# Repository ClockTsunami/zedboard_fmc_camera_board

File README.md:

zedboard_fmc_camera_board
=========================

fmc lpc camera board for zedboard

eagle library initially get from:

code.danstrother.com/eagle-lbr/dan-xilinx.lbr

https://github.com/zynqgeek/Zedboard-Eagle-Library.git

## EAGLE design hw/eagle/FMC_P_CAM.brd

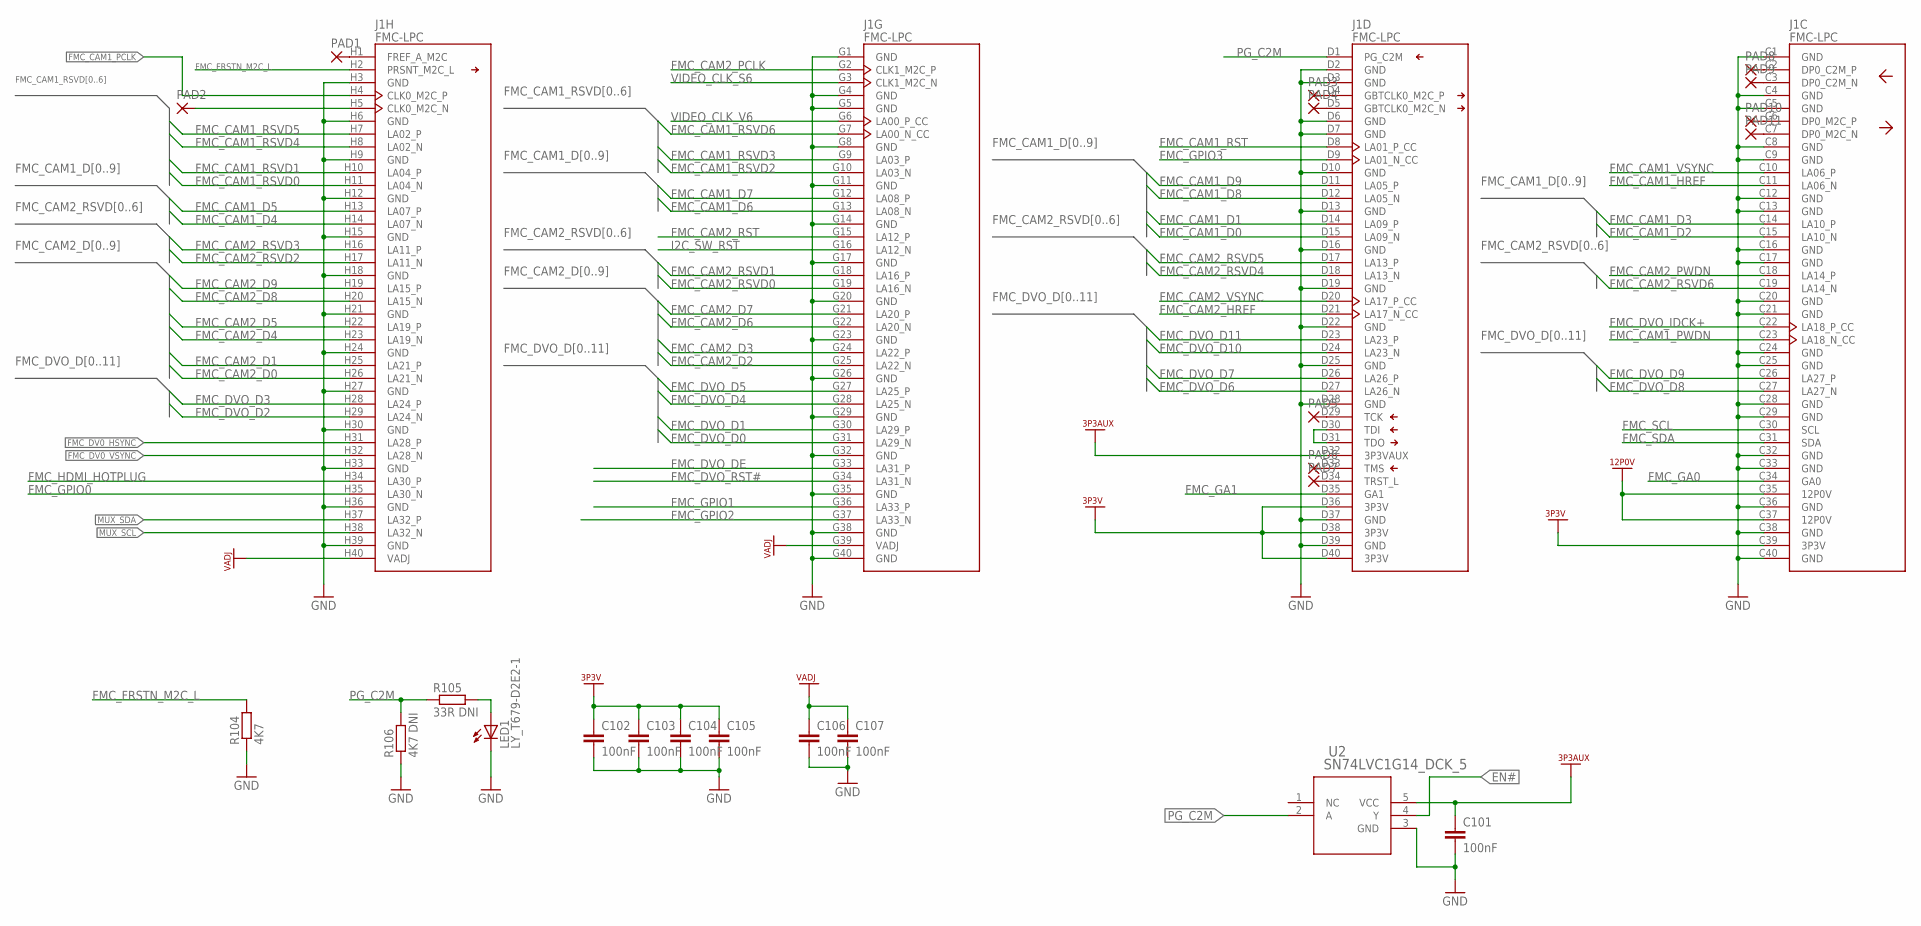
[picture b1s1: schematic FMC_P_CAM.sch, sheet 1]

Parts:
C101, C102, C103, C104, C105, C106, C107: 100nF; C0603
J1: FMC-LPC; FMC-LPC-MALE
LED1: LY_T679-D2E2-1; PLCC2
PAD1, PAD2, PAD3, PAD4, PAD5, PAD6, PAD7, PAD8, PAD9, PAD10, PAD11: 1,6/0,8
R104: 4K7; R0603
R105: 33R DNI; R0603
R106: 4K7 DNI; R0603
U2: SN74LVC1G14_DCK_5; DCK5

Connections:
3P3AUX: C101.1, J1.D32 (3P3VAUX), U2.5 (VCC)
3P3V: C102.1, C103.1, C104.1, C105.1, J1.C39 (3P3V), J1.D36 (3P3V), J1.D38 (3P3V), J1.D40 (3P3V); also elsewhere on the board
12P0V: J1.C35 (12P0V), J1.C37 (12P0V); also elsewhere on the board
EN#: U2.4 (Y); also elsewhere on the board
FMC_CAM1_D0: J1.D15 (LA09_N); also elsewhere on the board
FMC_CAM1_D1: J1.D14 (LA09_P); also elsewhere on the board
FMC_CAM1_D2: J1.C15 (LA10_N); also elsewhere on the board
FMC_CAM1_D3: J1.C14 (LA10_P); also elsewhere on the board
FMC_CAM1_D4: J1.H14 (LA07_N); also elsewhere on the board
FMC_CAM1_D5: J1.H13 (LA07_P); also elsewhere on the board
FMC_CAM1_D6: J1.G13 (LA08_N); also elsewhere on the board
FMC_CAM1_D7: J1.G12 (LA08_P); also elsewhere on the board
FMC_CAM1_D8: J1.D12 (LA05_N); also elsewhere on the board
FMC_CAM1_D9: J1.D11 (LA05_P); also elsewhere on the board
FMC_CAM1_HREF: J1.C11 (LA06_N); also elsewhere on the board
FMC_CAM1_PCLK: J1.H4 (CLK0_M2C_P); also elsewhere on the board
FMC_CAM1_PWDN: J1.C23 (LA18_N_CC); also elsewhere on the board
FMC_CAM1_RST: J1.D8 (LA01_P_CC); also elsewhere on the board
FMC_CAM1_RSVD0: J1.H11 (LA04_N); also elsewhere on the board
FMC_CAM1_RSVD1: J1.H10 (LA04_P); also elsewhere on the board
FMC_CAM1_RSVD2: J1.G10 (LA03_N); also elsewhere on the board
FMC_CAM1_RSVD3: J1.G9 (LA03_P); also elsewhere on the board
FMC_CAM1_RSVD4: J1.H8 (LA02_N); also elsewhere on the board
FMC_CAM1_RSVD5: J1.H7 (LA02_P); also elsewhere on the board
FMC_CAM1_RSVD6: J1.G7 (LA00_N_CC); also elsewhere on the board
FMC_CAM1_VSYNC: J1.C10 (LA06_P); also elsewhere on the board
FMC_CAM2_D0: J1.H26 (LA21_N); also elsewhere on the board
FMC_CAM2_D1: J1.H25 (LA21_P); also elsewhere on the board
FMC_CAM2_D2: J1.G25 (LA22_N); also elsewhere on the board
FMC_CAM2_D3: J1.G24 (LA22_P); also elsewhere on the board
FMC_CAM2_D4: J1.H23 (LA19_N); also elsewhere on the board
FMC_CAM2_D5: J1.H22 (LA19_P); also elsewhere on the board
FMC_CAM2_D6: J1.G22 (LA20_N); also elsewhere on the board
FMC_CAM2_D7: J1.G21 (LA20_P); also elsewhere on the board
FMC_CAM2_D8: J1.H20 (LA15_N); also elsewhere on the board
FMC_CAM2_D9: J1.H19 (LA15_P); also elsewhere on the board
FMC_CAM2_HREF: J1.D21 (LA17_N_CC); also elsewhere on the board
FMC_CAM2_PCLK: J1.G2 (CLK1_M2C_P); also elsewhere on the board
FMC_CAM2_PWDN: J1.C18 (LA14_P); also elsewhere on the board
FMC_CAM2_RST: J1.G15 (LA12_P); also elsewhere on the board
FMC_CAM2_RSVD0: J1.G19 (LA16_N); also elsewhere on the board
FMC_CAM2_RSVD1: J1.G18 (LA16_P); also elsewhere on the board
FMC_CAM2_RSVD2: J1.H17 (LA11_N); also elsewhere on the board
FMC_CAM2_RSVD3: J1.H16 (LA11_P); also elsewhere on the board
FMC_CAM2_RSVD4: J1.D18 (LA13_N); also elsewhere on the board
FMC_CAM2_RSVD5: J1.D17 (LA13_P); also elsewhere on the board
FMC_CAM2_RSVD6: J1.C19 (LA14_N); also elsewhere on the board
FMC_CAM2_VSYNC: J1.D20 (LA17_P_CC); also elsewhere on the board
FMC_DV0_HSYNC: J1.H31 (LA28_P)
FMC_DV0_VSYNC: J1.H32 (LA28_N)
FMC_DVO_D0: J1.G31 (LA29_N)
FMC_DVO_D1: J1.G30 (LA29_P)
FMC_DVO_D2: J1.H29 (LA24_N)
FMC_DVO_D3: J1.H28 (LA24_P)
FMC_DVO_D4: J1.G28 (LA25_N)
FMC_DVO_D5: J1.G27 (LA25_P)
FMC_DVO_D6: J1.D27 (LA26_N)
FMC_DVO_D7: J1.D26 (LA26_P)
FMC_DVO_D8: J1.C27 (LA27_N)
FMC_DVO_D9: J1.C26 (LA27_P)
FMC_DVO_D10: J1.D24 (LA23_N)
FMC_DVO_D11: J1.D23 (LA23_P)
FMC_DVO_DE: J1.G33 (LA31_P)
FMC_DVO_IDCK+: J1.C22 (LA18_P_CC)
FMC_DVO_RST#: J1.G34 (LA31_N)
FMC_FRSTN_M2C_L: J1.H2 (PRSNT_M2C_L), R104.2
FMC_GA0: J1.C34 (GA0)
FMC_GA1: J1.D35 (GA1)
FMC_GPIO0: J1.H35 (LA30_N)
FMC_GPIO1: J1.G36 (LA33_P)
FMC_GPIO2: J1.G37 (LA33_N)
FMC_GPIO3: J1.D9 (LA01_N_CC)
FMC_HDMI_HOTPLUG: J1.H34 (LA30_P)
FMC_SCL: J1.C30 (SCL)
FMC_SDA: J1.C31 (SDA)
GND: C101.2, C102.2, C103.2, C104.2, C105.2, C106.2, C107.2, J1.C1 (GND), J1.C4 (GND), J1.C5 (GND), J1.C8 (GND), J1.C9 (GND), J1.C12 (GND), J1.C13 (GND), J1.C16 (GND), J1.C17 (GND), J1.C20 (GND), J1.C21 (GND), J1.C24 (GND), J1.C25 (GND), J1.C28 (GND), J1.C29 (GND), J1.C32 (GND), J1.C33 (GND), J1.C36 (GND), J1.C38 (GND), J1.C40 (GND), J1.D2 (GND), J1.D3 (GND), J1.D6 (GND), J1.D7 (GND), J1.D10 (GND), J1.D13 (GND), J1.D16 (GND), J1.D19 (GND), J1.D22 (GND), J1.D25 (GND), J1.D28 (GND), J1.D37 (GND), J1.D39 (GND), J1.G1 (GND), J1.G4 (GND), J1.G5 (GND), J1.G8 (GND), J1.G11 (GND), J1.G14 (GND), J1.G17 (GND), J1.G20 (GND), J1.G23 (GND), J1.G26 (GND), J1.G29 (GND), J1.G32 (GND), J1.G35 (GND), J1.G38 (GND), J1.G40 (GND), J1.H3 (GND), J1.H6 (GND), J1.H9 (GND), J1.H12 (GND), J1.H15 (GND), J1.H18 (GND), J1.H21 (GND), J1.H24 (GND), J1.H27 (GND), J1.H30 (GND), J1.H33 (GND), J1.H36 (GND), J1.H39 (GND), LED1.C, R104.1, R106.1, U2.3 (GND); also elsewhere on the board
I2C_SW_RST: J1.G16 (LA12_N); also elsewhere on the board
MUX_SCL: J1.H38 (LA32_N); also elsewhere on the board
MUX_SDA: J1.H37 (LA32_P); also elsewhere on the board
unnamed: J1.H5 (CLK0_M2C_N), PAD2.1
unnamed: LED1.A, R105.2
unnamed: J1.D30 (TDI), J1.D31 (TDO)
unnamed: J1.H1 (FREF_A_M2C), PAD1.1
unnamed: J1.D4 (GBTCLK0_M2C_P), PAD3.1
unnamed: J1.D5 (GBTCLK0_M2C_N), PAD4.1
unnamed: J1.D29 (TCK), PAD5.1
unnamed: J1.D33 (TMS), PAD6.1
unnamed: J1.D34 (TRST_L), PAD7.1
unnamed: J1.C2 (DP0_C2M_P), PAD8.1
unnamed: J1.C3 (DP0_C2M_N), PAD9.1
unnamed: J1.C6 (DP0_M2C_P), PAD10.1
unnamed: J1.C7 (DP0_M2C_N), PAD11.1
PG_C2M: J1.D1 (PG_C2M), R105.1, R106.2, U2.2 (A)
VADJ: C106.1, C107.1, J1.G39 (VADJ), J1.H40 (VADJ); also elsewhere on the board
VIDEO_CLK_S6: J1.G3 (CLK1_M2C_N)
VIDEO_CLK_V6: J1.G6 (LA00_P_CC)

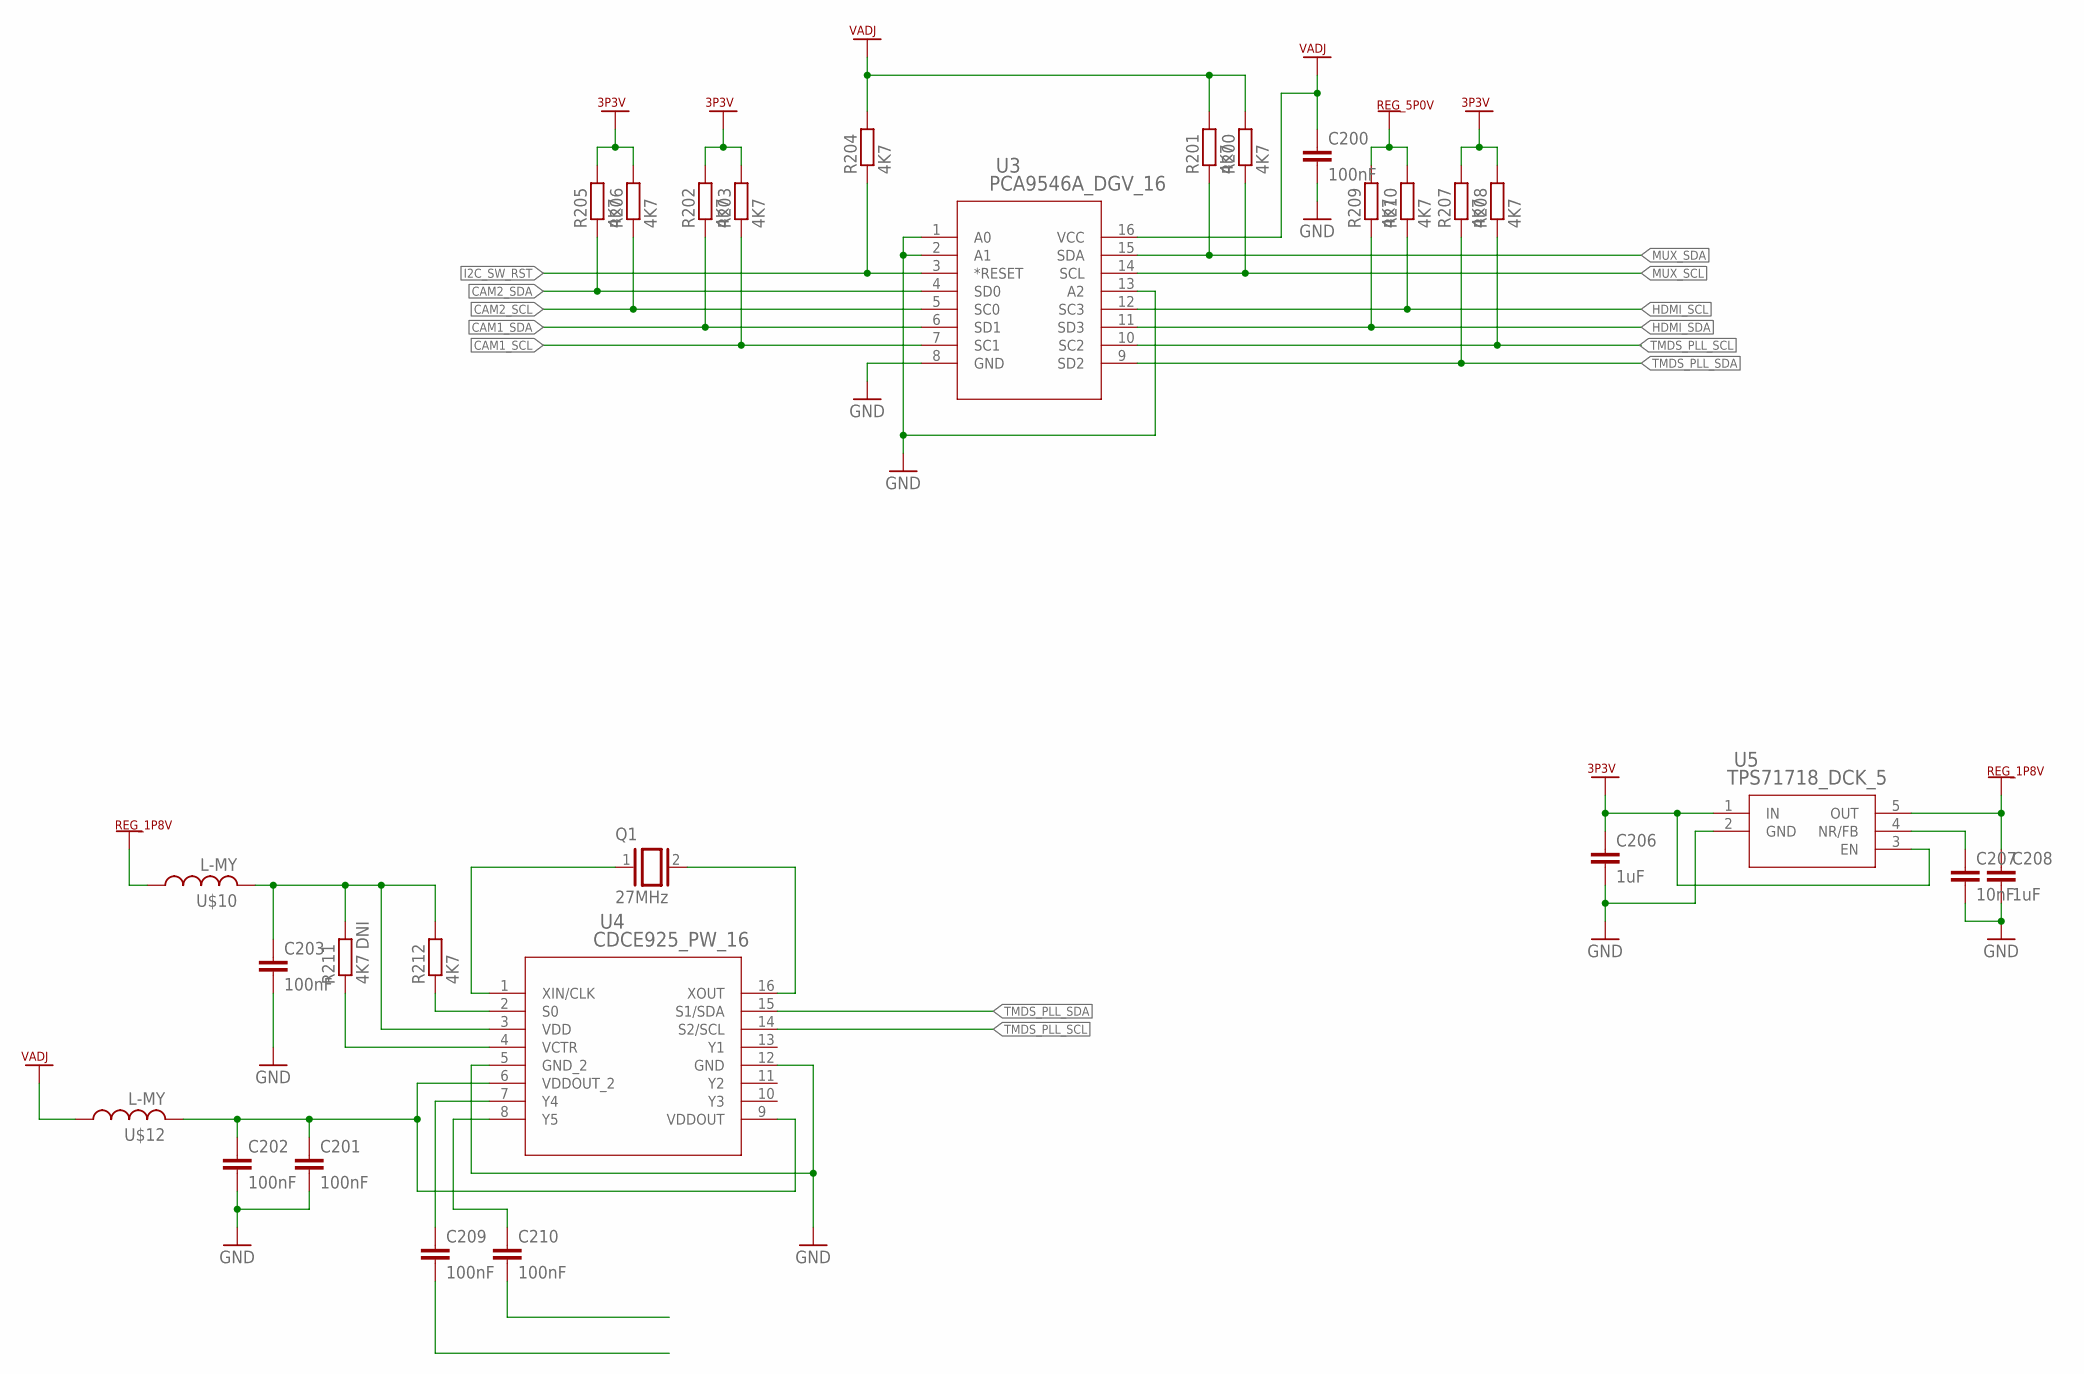
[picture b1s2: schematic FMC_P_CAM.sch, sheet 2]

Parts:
C200, C201, C202, C203, C209, C210: 100nF; C0603
C206, C208: 1uF; C0603
C207: 10nF; C0603
Q1: 27MHz; Q
R200, R201, R202, R203, R204, R205, R206, R207, R208, R209, R210, R212: 4K7; R0603
R211: 4K7 DNI; R0603
U3: PCA9546A_DGV_16; DGV16
U4: CDCE925_PW_16; PW16
U5: TPS71718_DCK_5; DCK5
U$10, U$12: L-MY; R0603

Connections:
3P3V: C206.1, R202.2, R203.2, R205.2, R206.2, R207.2, R208.2, U5.1 (IN), U5.3 (EN); also elsewhere on the board
CAM1_SCL: R203.1, U3.7 (SC1)
CAM1_SDA: R202.1, U3.6 (SD1)
CAM1_XCLK: C210.2
CAM2_SCL: R206.1, U3.5 (SC0)
CAM2_SDA: R205.1, U3.4 (SD0)
CAM2_XCLK: C209.2
GND: C200.2, C201.2, C202.2, C203.2, C206.2, C207.2, C208.2, U3.1 (A0), U3.2 (A1), U3.8 (GND), U3.13 (A2), U4.5 (GND_2), U4.12 (GND), U5.2 (GND); also elsewhere on the board
HDMI_SCL: R210.1, U3.12 (SC3)
HDMI_SDA: R209.1, U3.11 (SD3)
I2C_SW_RST: R204.1, U3.3 (*RESET); also elsewhere on the board
MUX_SCL: R200.1, U3.14 (SCL); also elsewhere on the board
MUX_SDA: R201.1, U3.15 (SDA); also elsewhere on the board
unnamed: Q1.1, U4.1 (XIN/CLK)
unnamed: Q1.2, U4.16 (XOUT)
unnamed: C203.1, R211.2, R212.2, U4.3 (VDD), U$10.2
unnamed: R212.1, U4.2 (S0)
unnamed: R211.1, U4.4 (VCTR)
unnamed: C201.1, C202.1, U4.6 (VDDOUT_2), U4.9 (VDDOUT), U$12.2
unnamed: C209.1, U4.7 (Y4)
unnamed: C210.1, U4.8 (Y5)
unnamed: C207.1, U5.4 (NR/FB)
REG_1P8V: C208.1, U5.5 (OUT), U$10.1
REG_5P0V: R209.2, R210.2; also elsewhere on the board
TMDS_PLL_SCL: R208.1, U3.10 (SC2), U4.14 (S2/SCL)
TMDS_PLL_SDA: R207.1, U3.9 (SD2), U4.15 (S1/SDA)
VADJ: C200.1, R200.2, R201.2, R204.2, U3.16 (VCC), U$12.1; also elsewhere on the board

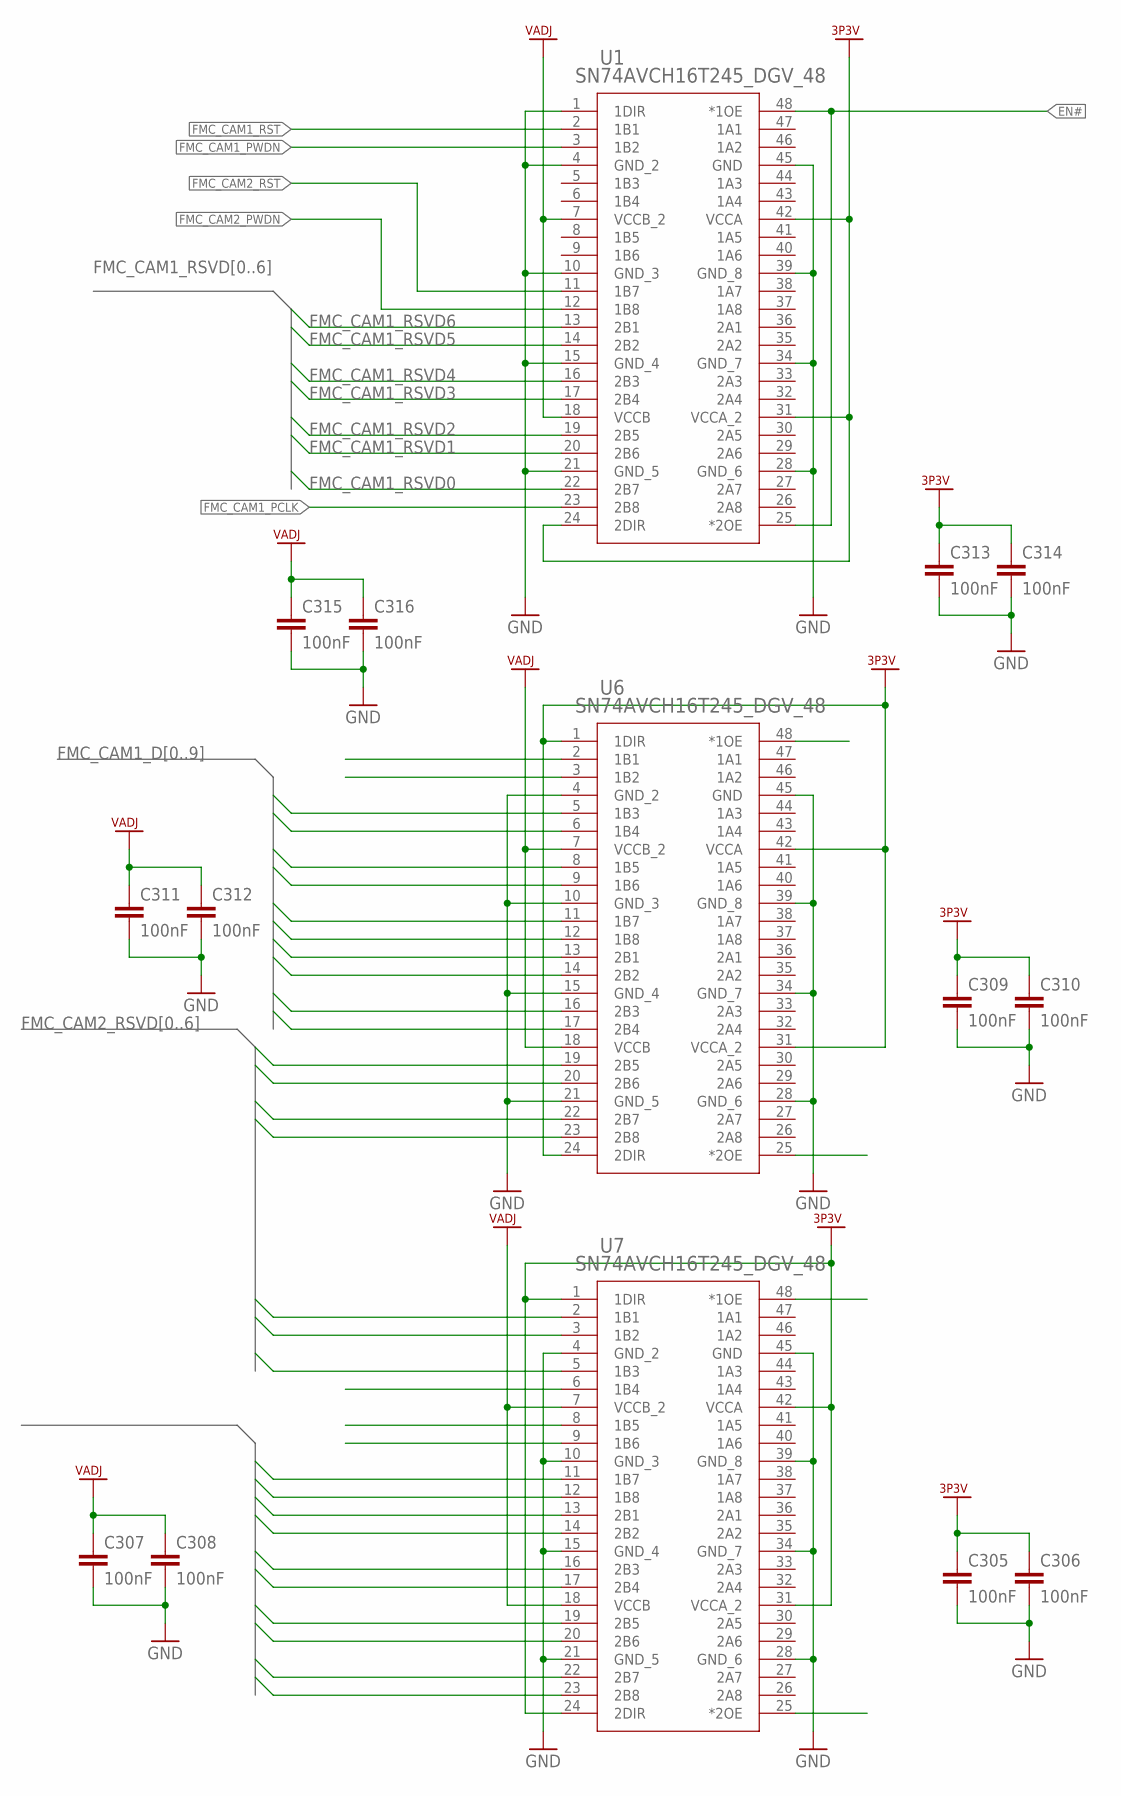
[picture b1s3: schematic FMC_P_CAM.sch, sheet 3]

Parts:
C305, C306, C307, C308, C309, C310, C311, C312, C313, C314, C315, C316: 100nF; C0603
U1, U6, U7: SN74AVCH16T245_DGV_48; DGV48

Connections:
3P3V: C305.1, C306.1, C309.1, C310.1, C313.1, C314.1, U1.24 (2DIR), U1.31 (VCCA_2), U1.42 (VCCA), U6.1 (1DIR), U6.24 (2DIR), U6.31 (VCCA_2), U6.42 (VCCA), U7.1 (1DIR), U7.24 (2DIR), U7.31 (VCCA_2), U7.42 (VCCA); also elsewhere on the board
EN#: U1.25 (*2OE), U1.48 (*1OE), U6.25 (*2OE), U6.48 (*1OE), U7.25 (*2OE), U7.48 (*1OE); also elsewhere on the board
FMC_CAM1_D0: U6.17 (2B4); also elsewhere on the board
FMC_CAM1_D1: U6.16 (2B3); also elsewhere on the board
FMC_CAM1_D2: U6.14 (2B2); also elsewhere on the board
FMC_CAM1_D3: U6.13 (2B1); also elsewhere on the board
FMC_CAM1_D4: U6.12 (1B8); also elsewhere on the board
FMC_CAM1_D5: U6.11 (1B7); also elsewhere on the board
FMC_CAM1_D6: U6.9 (1B6); also elsewhere on the board
FMC_CAM1_D7: U6.8 (1B5); also elsewhere on the board
FMC_CAM1_D8: U6.6 (1B4); also elsewhere on the board
FMC_CAM1_D9: U6.5 (1B3); also elsewhere on the board
FMC_CAM1_HREF: U6.3 (1B2); also elsewhere on the board
FMC_CAM1_PCLK: U1.23 (2B8); also elsewhere on the board
FMC_CAM1_PWDN: U1.3 (1B2); also elsewhere on the board
FMC_CAM1_RST: U1.2 (1B1); also elsewhere on the board
FMC_CAM1_RSVD0: U1.22 (2B7); also elsewhere on the board
FMC_CAM1_RSVD1: U1.20 (2B6); also elsewhere on the board
FMC_CAM1_RSVD2: U1.19 (2B5); also elsewhere on the board
FMC_CAM1_RSVD3: U1.17 (2B4); also elsewhere on the board
FMC_CAM1_RSVD4: U1.16 (2B3); also elsewhere on the board
FMC_CAM1_RSVD5: U1.14 (2B2); also elsewhere on the board
FMC_CAM1_RSVD6: U1.13 (2B1); also elsewhere on the board
FMC_CAM1_VSYNC: U6.2 (1B1); also elsewhere on the board
FMC_CAM2_D0: U7.23 (2B8); also elsewhere on the board
FMC_CAM2_D1: U7.22 (2B7); also elsewhere on the board
FMC_CAM2_D2: U7.20 (2B6); also elsewhere on the board
FMC_CAM2_D3: U7.19 (2B5); also elsewhere on the board
FMC_CAM2_D4: U7.17 (2B4); also elsewhere on the board
FMC_CAM2_D5: U7.16 (2B3); also elsewhere on the board
FMC_CAM2_D6: U7.14 (2B2); also elsewhere on the board
FMC_CAM2_D7: U7.13 (2B1); also elsewhere on the board
FMC_CAM2_D8: U7.12 (1B8); also elsewhere on the board
FMC_CAM2_D9: U7.11 (1B7); also elsewhere on the board
FMC_CAM2_HREF: U7.9 (1B6); also elsewhere on the board
FMC_CAM2_PCLK: U7.6 (1B4); also elsewhere on the board
FMC_CAM2_PWDN: U1.12 (1B8); also elsewhere on the board
FMC_CAM2_RST: U1.11 (1B7); also elsewhere on the board
FMC_CAM2_RSVD0: U7.5 (1B3); also elsewhere on the board
FMC_CAM2_RSVD1: U7.3 (1B2); also elsewhere on the board
FMC_CAM2_RSVD2: U7.2 (1B1); also elsewhere on the board
FMC_CAM2_RSVD3: U6.23 (2B8); also elsewhere on the board
FMC_CAM2_RSVD4: U6.22 (2B7); also elsewhere on the board
FMC_CAM2_RSVD5: U6.20 (2B6); also elsewhere on the board
FMC_CAM2_RSVD6: U6.19 (2B5); also elsewhere on the board
FMC_CAM2_VSYNC: U7.8 (1B5); also elsewhere on the board
GND: C305.2, C306.2, C307.2, C308.2, C309.2, C310.2, C311.2, C312.2, C313.2, C314.2, C315.2, C316.2, U1.1 (1DIR), U1.4 (GND_2), U1.10 (GND_3), U1.15 (GND_4), U1.21 (GND_5), U1.28 (GND_6), U1.34 (GND_7), U1.39 (GND_8), U1.45 (GND), U6.4 (GND_2), U6.10 (GND_3), U6.15 (GND_4), U6.21 (GND_5), U6.28 (GND_6), U6.34 (GND_7), U6.39 (GND_8), U6.45 (GND), U7.4 (GND_2), U7.10 (GND_3), U7.15 (GND_4), U7.21 (GND_5), U7.28 (GND_6), U7.34 (GND_7), U7.39 (GND_8), U7.45 (GND); also elsewhere on the board
VADJ: C307.1, C308.1, C311.1, C312.1, C315.1, C316.1, U1.7 (VCCB_2), U1.18 (VCCB), U6.7 (VCCB_2), U6.18 (VCCB), U7.7 (VCCB_2), U7.18 (VCCB); also elsewhere on the board

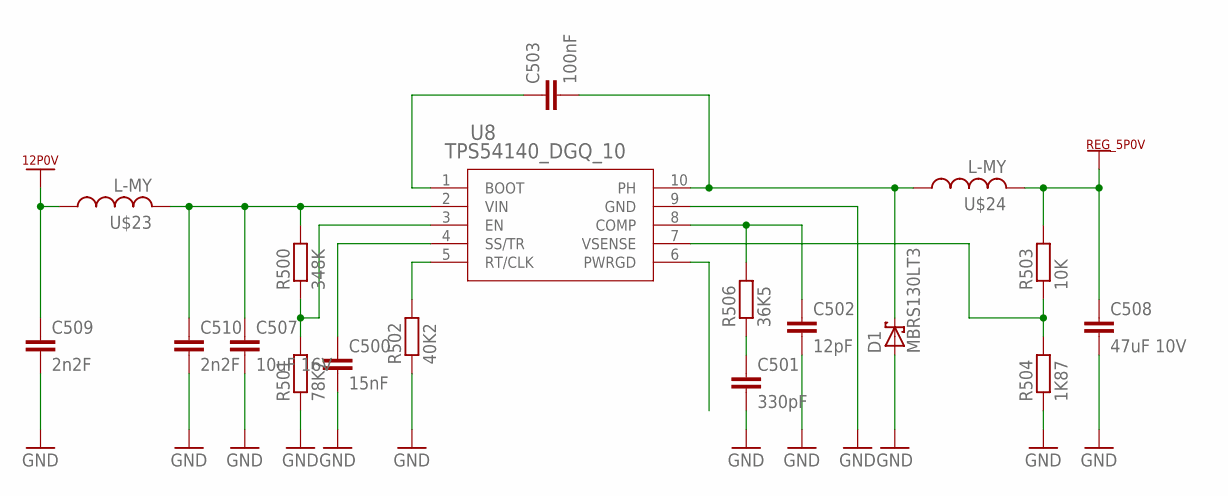
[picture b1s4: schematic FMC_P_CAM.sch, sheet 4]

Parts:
C500: 15nF; C0603
C501: 330pF; C0603
C502: 12pF; C0603
C503: 100nF; C0603
C507: 10uF 16V; C0603
C508: 47uF 10V; C0603
C509, C510: 2n2F; C0603
D1: MBRS130LT3; SMB
R500: 348K; R0603
R501: 78K7; R0603
R502: 40K2; R0603
R503: 10K; R0603
R504: 1K87; R0603
R506: 36K5; R0603
U8: TPS54140_DGQ_10; DGQ10_1P88X1P57
U$23, U$24: L-MY; R0603

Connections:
12P0V: C509.1, U$23.1; also elsewhere on the board
GND: C500.2, C501.2, C502.2, C507.2, C508.2, C509.2, C510.2, D1.A, R501.1, R502.1, R504.1, U8.9 (GND); also elsewhere on the board
unnamed: C507.1, C510.1, R500.2, U8.2 (VIN), U$23.2
unnamed: C503.1, U8.1 (BOOT)
unnamed: C503.2, D1.C, U8.10 (PH), U$24.1
unnamed: R500.1, R501.2, U8.3 (EN)
unnamed: C500.1, U8.4 (SS/TR)
unnamed: R502.2, U8.5 (RT/CLK)
unnamed: C502.1, R506.2, U8.8 (COMP)
unnamed: C501.1, R506.1
unnamed: R503.1, R504.2, U8.7 (VSENSE)
PGOOD: U8.6 (PWRGD)
REG_5P0V: C508.1, R503.2, U$24.2; also elsewhere on the board

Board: 2 copper layers, 85 parts (3 on the bottom side), 96 nets, no tracks yet.

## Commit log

2013-09-18 add eagle fmc library
2013-09-18 add eagle schematic
2013-09-20 update board
2013-09-20 update schematic
2013-09-22 add libraries
2013-09-22 add user defined library
2013-09-22 move lbr to lib dir
2013-09-22 update CDCE925_PW_16 library
2013-09-22 update SN74LVC1G14_DCK_5 library
2013-09-22 update PCA9546A_DGV_16 library
2013-09-22 update TPS71718_DCK_5 library
2013-09-22 update SN74AVCH16T245_DGV_48 library
2013-09-22 update TPS54140_DGQ_10 library
2013-09-22 add new supply symbol
2013-09-22 update symbol
2013-09-22 update board schematic
2013-09-23 add design libraries
2013-09-23 update FMC female connector
2013-09-23 add ds SN74LVC1G14DCK library
2013-09-23 add my common library
2013-09-23 add DesignSpark SN74AVCH16T245DGV library
2013-09-23 add DesignSpark project
2013-09-24 add ad CDCE925PW library
2013-09-24 add ad SN74AVC20T245DG library
2013-09-24 update ad SN74AVC20T245DG library
2013-09-24 rename SN74AVC20T245DG to SN74AVC20T245DGV
2013-09-24 add ad library SN74AVCH16T245DGV
2013-09-24 add ad SN74CB3T1G125DCK library
2013-09-24 add ad SN74LVC1G14DCK
2013-09-24 add ad TFP410PAP library
2013-09-24 add ad TPS22942DCK library
2013-09-24 add ad TXS0104EPW library
2013-09-24 add ad PCA9546ADGV library
2013-09-24 add ad TPS71718DCK library
2013-09-25 add ds PCA9546ADGV library
2013-09-25 update ds schematic file
2013-09-25 add new ds libs
2013-09-25 update fmc_p_cam libs
2013-09-25 update mycommon libs
2013-09-25 update ds schematic
2013-09-25 add ad file
2013-09-26 add ds TPS54140DGQ library
2013-09-26 add ds CDCE925PW library
2013-09-26 add ds SN74AVC20T245DGV library
2013-09-26 add ds SN74CB3T1G125DCK library
2013-09-26 add TFP410PAP library
2013-09-26 add ds TPS22942DCK library
2013-09-26 add ds TXS0104EPW library
2013-09-26 update connector package
2013-09-26 update ds mycommon library
2013-09-27 add FMC_CONNECTOR ad library
2013-09-27 update ad project
2013-09-27 rename ad Sheet1
2013-09-27 update ad board
